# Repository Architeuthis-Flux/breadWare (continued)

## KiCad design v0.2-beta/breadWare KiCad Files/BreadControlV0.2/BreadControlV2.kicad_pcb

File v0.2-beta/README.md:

# breadWare v0.2

Here's the second board revision. I was showing the last version off to someone and they offhandedly mentioned that it would be cool if the whole thing fit under the breadboard. I knew this was my plan all along, but it forced me to finally design it before the code gets too specific to the original off-the-cuff design and I get stuck with my poor ~~life~~ design choices. 

## Matrix Board Changes

I found that the most valuable resource when finding paths between rows that aren't directly connected (so they need to make an intermediate hop) are "virtual" breadboard rows that aren't connected to the actual board but connect to the control board below and basically act as the general purpose nodes to do everything else (like reading voltages, connecting to the GPIO on the microcontroller, connecting to a second board, etc.). I put 4 of them in (on chips A, D, E, H), and I don't think that's nearly enough if I want to be able to do a bunch of special function things at once without making the user use some particular set of rows to do certain things. I would really like to make it as simple as "put anything wherever and the board will figure it out."

I changed the logical arrangement of the [MT8816](https://www.futurlec.com/Datasheet/Zarlink/MT8816AE.pdf) crosspoint switches to make the it easier to just hop over the middle space. In the original layout if I wanted to connect top row 5 to bottom row 5, it would always take 2 hops to do that (and these switches each have an on resistance of about 65Ω). Now the bottom rows are flipped so internally the bottom left is 62 and counts down to 33 on the right (note: these are abstracted away to the user by using b1-b30 instead of bigger numbers.)

And just to add some glam I added some reverse mounted LEDs that shine through the top and bottom power rails to show when that rail's power supply is on.

## Control Board Changes

I almost entirely redesigned the controller board so it has a ton of whatever the hardware equivalent of syntactic sugar is. The original was kind of thrown together to make sure the concept of using crosspoint switches like that wasn't fundamentally stupid (still not entirely ruling that out, but so far it looks promising.) I also just realized I never did a writeup for the first iteration, and I'm not about to go back and do that just to prove that this board is an improvement.

### Power Stuff
Because I'm going to such great lengths to make everything analog, and I already need a negative supply for the crosspoint switches; I decided to make the adjustable power supply for the rails also be able to do negative voltages. The power stuff still needs some work, right now it gets pretty warm when it's running and it really doesn't like it when I remove the matrix board with it on. Presumably because it needs some current draw but I'm not exactly sure why it cares as much as it does (I burned a tantalum cap shaped brand into my finger, you could almost read the markings in it.) 

Also, the range of voltages available to each of the 4 rails is fixed. Next revision might include some way to multiplex the power rails (allowing any of them to be negative, right now only the bottom negative rail can do that and it can be changed with a solder jumper) but having looked into it for a while, there doesn't seem to be a way to do it simply enough to outweigh the small utility gained from it. If anyone knows a better way to do this, let me know.

I'm using an [LT1054](https://www.ti.com/lit/ds/symlink/lt1054.pdf?ts=1623386605661&ref_url=https%253A%252F%252Fwww.ti.com%252Fproduct%252FLT1054%253Futm_source%253Dgoogle%2526utm_medium%253Dcpc%2526utm_campaign%253Dapp-null-null-GPN_EN-cpc-pf-google-sa%2526utm_content%253DLT1054%2526ds_k%253DLT1054%2526DCM%253Dyes%2526gclid%253DCj0KCQjw8IaGBhCHARIsAGIRRYqazWa1HYDDSNdHtIH7dqU-yqDqCnm6CfqRnDNBBC_sS4i2s7MQtgcaAuJ-EALw_wcB%2526gclsrc%253Daw.ds) switched capacitor bipolar voltage converter that takes in +5V and doubles it to +10V and also flips that to -10V. That powers the MT8816s directly and the op amps I'm using for the adjustable voltage supplies. The previous board used inductors for that, and aside from the electrical noise, you could hear them running. I know the frequency they run at is way higher than 20kHz but they must have been resonating with something (or I'm actually part bat) because it was super annoying.

The way I decided to make an adjustable supply that can be controlled by the mcu might be really dumb, but so far it seems to work. I didn't find any well documented examples of people doing it this way, so I'd love to hear from anyone who has or has a good reason why it will cause problems. 

I used an [MCP4728](http://ww1.microchip.com/downloads/en/devicedoc/22187e.pdf) DAC that's controlled by I2C and feeds it's 4 outputs into 2 [L272D](https://www.st.com/resource/en/datasheet/l272.pdf) power op amps that can apparently supply 1A each. I used the inverting arrangement with a gain of 1.6 to make the negative supply able to supply 0V - -8V from the 0V - +5V output from the DAC. I put a bunch of low voltage drop schottkys (or is it schottkies? weird) so whatever is happening on the power rails they're supplying shouldn't affect them too much. 

What's cool about this setup is that the DAC is fast enough to use this whole circuit as a DDS function generator. That's why I put solder jumpers to disconnect all the bypass caps. I haven't written the code to try this out yet though. 

### Special Functions

On the control board there's another 8x16 crosspoint switch that I'm using to multiplex the 8 passthrough connections (1 per chip on the top matrix board, but only 4 of them aren't connected to a breadboard pin) to the special functions on the bottom control board. 

The special functions are (a checkmark means the firmware is written enough to use it):
 [  ] 2 ADC channels that can be read by the microcontroller 
 [x] 2 digital potentiometer channels using an [MCP4661](https://ww1.microchip.com/downloads/en/DeviceDoc/22107B.pdf) 
 [  ] 5 GPIO pins directly connected to the [ATmega4809](http://ww1.microchip.com/downloads/en/DeviceDoc/ATmega4808-4809-Data-Sheet-DS40002173A.pdf)
 [x] 2 adjustable power supply channels (0 - 5V, 0 - -8V)
 [x] 1 ground

The 2 ADC channels go through two 4:1 voltage dividers to bring a possible ±10V input down to ±2.5V and the bottom of those dividers are connected to the V_REF pin on the microcontroller so analog signals can be biased to 0-5V to be read by the 10-bit ADC. 

There's an [MCP4661](https://ww1.microchip.com/downloads/en/DeviceDoc/22107B.pdf) dual 8 bit digital potentiometer that has all 3 pins on 2 independent pots connected to the special function switch. I need to come up with a better interface for setting it in the terminal menu. When I eventually get around to making a GUI for this it will definitely make these more useful. These also come in 4 different ranges (5K, 10K, 50K, 100K) with the same pinout, I currently have the 50K model in there so that means each step is 195 ohms.

The GPIO pins are super interesting, for some reason the [ATmega4809](http://ww1.microchip.com/downloads/en/DeviceDoc/ATmega4808-4809-Data-Sheet-DS40002173A.pdf) datasheet never mentions the clear superiority of the first 4 pins in port C. 

PC0-3 can do I2C, U(S)ART, 16-bit Timer/Counter, PWM, SPI, and CCL-LUT! 
The CCL-LUT means Configurable Custom Logic - LookUp Table, so that means it an simulate an arbitrary logic gate. The analog stuff is covered by pin PE3. 

Now the tricky part is coming up with a nice way to use those functions through the serial connection. I could probably somehow port the Bus Pirate firmware into some sort of shell, so you could use their awesome Community Firmware (and the red PCB really sells the aesthetic.) 

Also, if anyone from Dangerous Prototypes is reading this; I'm dying for updates on (or just an official crushing of my dreams of one day owning) the [Bus Pirate Ultra](http://dangerousprototypes.com/forum/index.php?topic=10316.0)

### Communicating With Other Things

On each corner of the board I put a 2x2 header so you can connect these side-by-side and make these into longer board. They communicate via UART with Tx Rx in at the top left and Tx Rx out at the top right. The bottom corners have the 4 unconnected pins from the top matrix on both sides. So you could use these to make connections from one board to the other. As it is currently, having only 4 of these general purpose matrix connections is a huge bottleneck for doing just about anything so I probably need to come up with a way to have more of these free pins in the next revision. 

To communicate with the computer, I'm using an [MCP2221A](http://ww1.microchip.com/downloads/en/devicedoc/20005565b.pdf) to talk to the mcu via a dedicated UART. That chip is also connected to the I2C lines but I'm not sure what I'm going to use that for, maybe I'll have the I2C traffic passed along in some sort of debug mode. It also can send a reset signal from one of it's 4 GPIO lines to the ATmega4809 (with a solder jumper in case that causes problems), which notably is a missing feature of this chip. 
I could pretend that my choice to to use this was some principled stand against FTDI to cover for the fact that I actually don't remember why I chose this over and FTDI232.

## Making It Do Stuff

The interface currently sort of follows the general format that a Bus Pirate (and I'm sure a bunch of other things) use; mostly single character commands that present a sub menu. It's amazing how quickly you run out of letters that make sense for a particular command, especially when you have some command you want to be available globally. 

Making connections on the board just requires you to type in the two rows you want to connect, separated by a comma. Rows on the bottom are preceded by a 'b' so if you want to connect the 12th row on the top to the 24th row on the bottom you just type
 > 12,b24

In the near future I intend to make a full blown GUI for this, because that's the part that will make this thing actually make your life easier.

Here are some screenshots the interface:

Connecting Nodes

Disconnecting Nodes

Turning on the power supplies

Using the potentiometer

Showing the frontend connections you've made

Showing the backend (chip to chip) connections

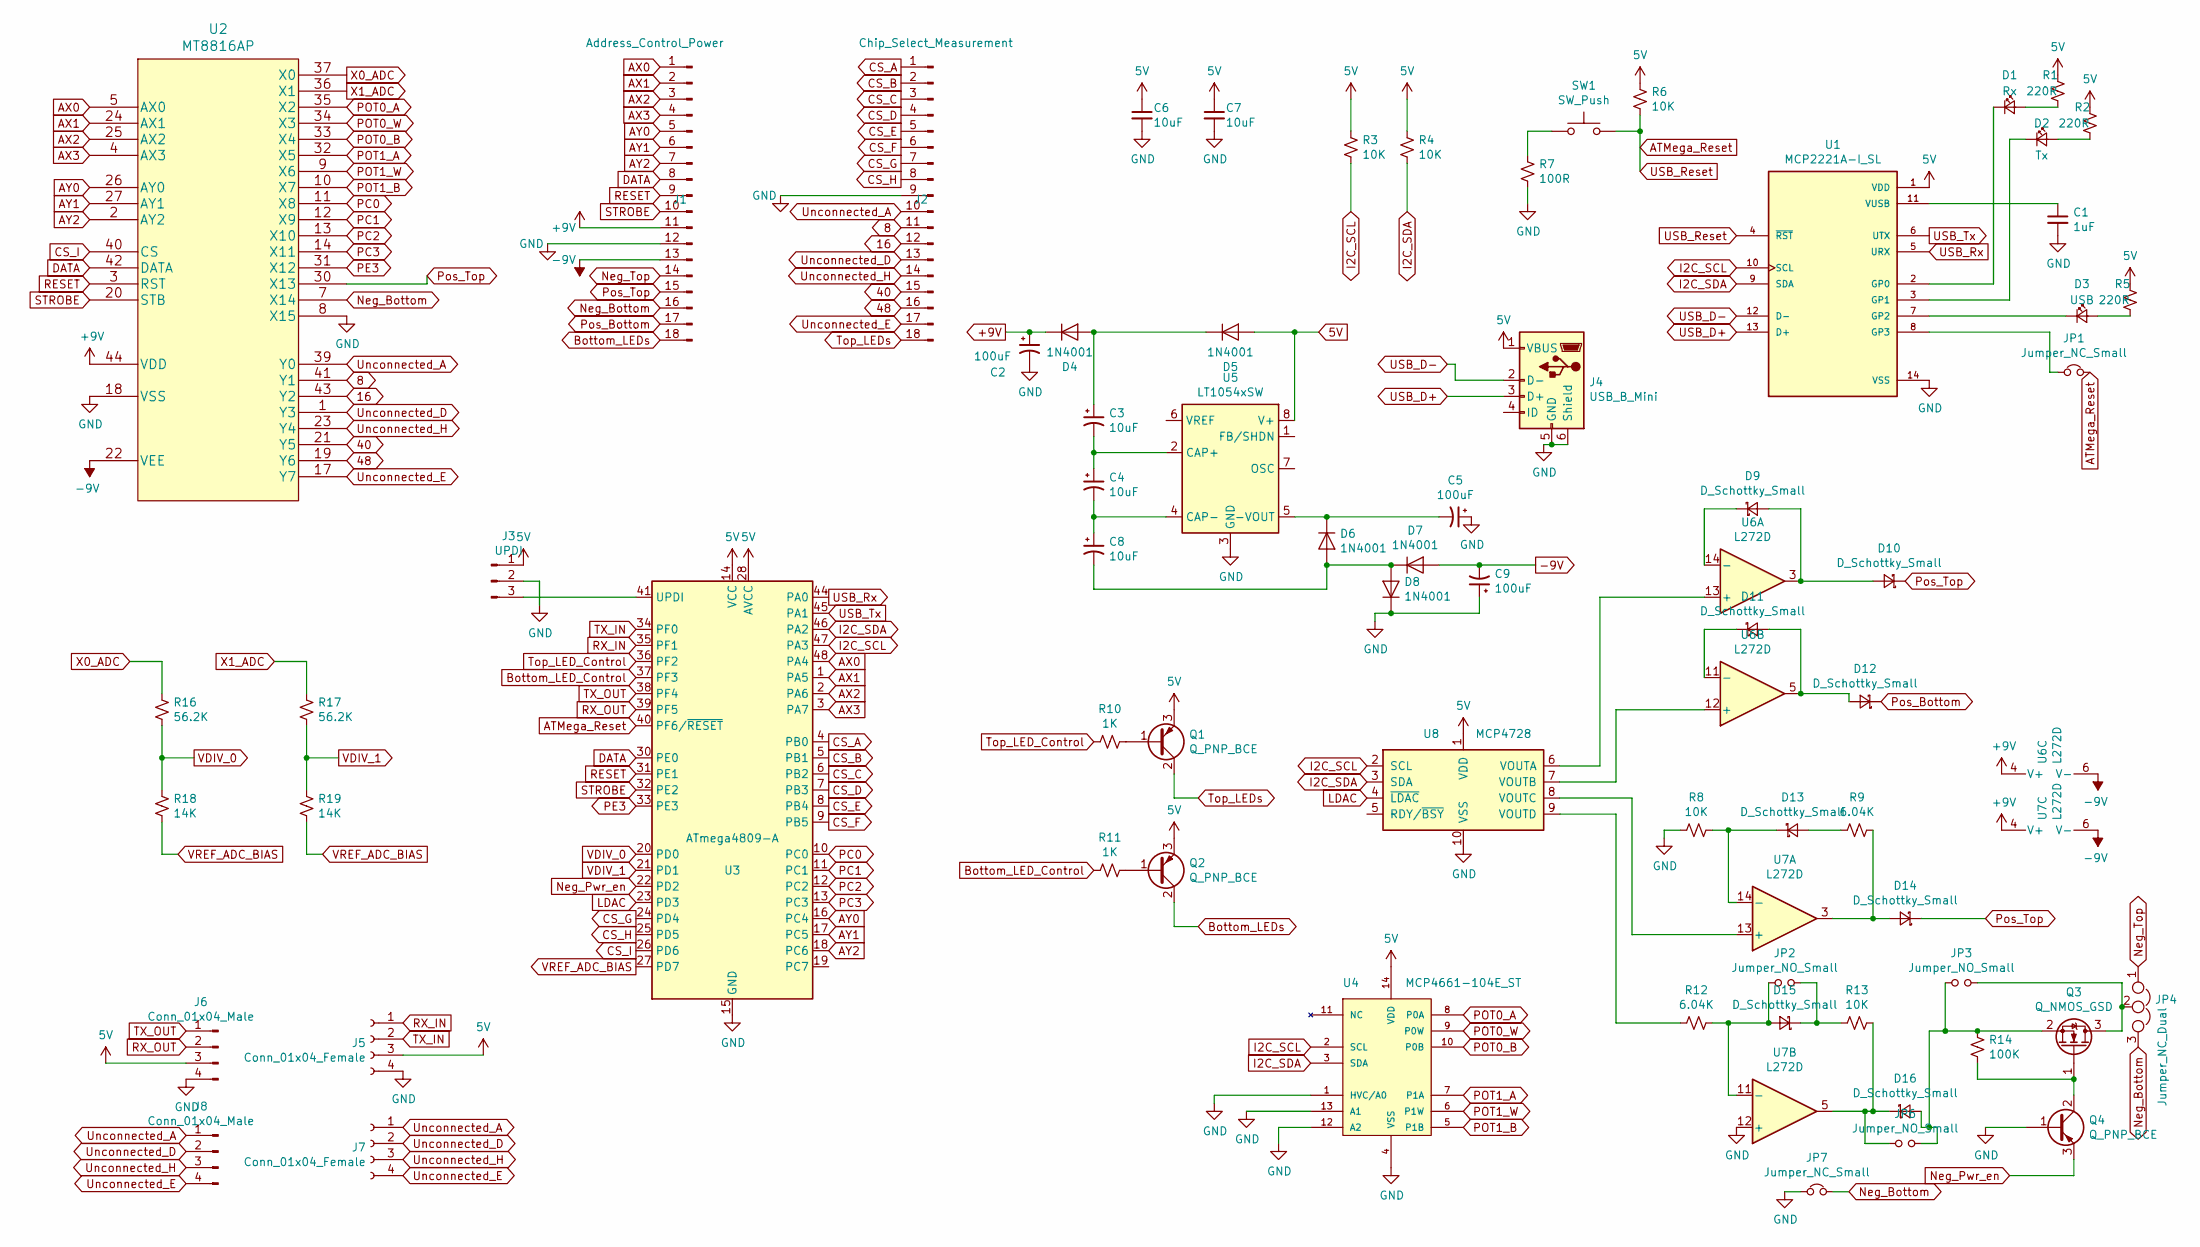
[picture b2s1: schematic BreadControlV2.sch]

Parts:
C1: 1uF; C_0805_2012Metric_Pad1.15x1.40mm_HandSolder
C2, C5, C9: 100uF; C_1206_3216Metric_Pad1.42x1.75mm_HandSolder
C3, C4, C8: 10uF; CP_EIA-6032-20_AVX-F_Pad2.25x2.35mm_HandSolder
C6, C7: 10uF; C_0805_2012Metric_Pad1.15x1.40mm_HandSolder
D1: Rx; D_0603_1608Metric_Pad1.05x0.95mm_HandSolder
D2: Tx; D_0603_1608Metric_Pad1.05x0.95mm_HandSolder
D3: USB; D_0603_1608Metric_Pad1.05x0.95mm_HandSolder
D4, D5, D6, D7, D8: 1N4001; D_SOD-123
D9, D10, D11, D12, D13, D14, D15, D16: D_Schottky_Small; D_SMB
J1: Address_Control_Power; PinHeader_1x18_P2.54mm_Vertical
J2: Chip_Select_Measurement; PinHeader_1x18_P2.54mm_Vertical
J3: UPDI; PinHeader_1x03_P2.54mm_Vertical
J4: USB_B_Mini; AMPHENOL_10033526-N3212LF
J5, J7: Conn_01x04_Female; PinHeader_2x02_P2.54mm_Horizontal
J6, J8: Conn_01x04_Male; PinHeader_2x02_P2.54mm_Horizontal
JP1, JP7: Jumper_NC_Small; SolderJumper-2_P1.3mm_Bridged_RoundedPad1.0x1.5mm
JP2, JP3, JP6: Jumper_NO_Small; SolderJumper-2_P1.3mm_Open_RoundedPad1.0x1.5mm
JP4: Jumper_NC_Dual; SolderJumper-3_P1.3mm_Bridged12_RoundedPad1.0x1.5mm_NumberL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
Q1, Q2, Q4: Q_PNP_BCE; SOT-23
Q3: Q_NMOS_GSD; SOT-23
R1, R2, R5: 220R; R_0805_2012Metric_Pad1.15x1.40mm_HandSolder
R3, R4, R6, R8, R13: 10K; R_0805_2012Metric_Pad1.15x1.40mm_HandSolder
R7: 100R; R_0805_2012Metric_Pad1.15x1.40mm_HandSolder
R9, R12: 6.04K; R_0805_2012Metric_Pad1.15x1.40mm_HandSolder
R10, R11: 1K; R_0805_2012Metric_Pad1.15x1.40mm_HandSolder
R14: 100K; R_0805_2012Metric_Pad1.15x1.40mm_HandSolder
R16, R17: 56.2K; R_0805_2012Metric_Pad1.15x1.40mm_HandSolder
R18, R19: 14K; R_0805_2012Metric_Pad1.15x1.40mm_HandSolder
SW1: SW_Push; SW_SPST_PTS645
U1: MCP2221A-I_SL; SOIC-14_3.9x8.7mm_P1.27mm
U2: MT8816AP; PLCC-44_16.6x16.6mm_P1.27mm
U3: ATmega4809-A; TQFP-48_7x7mm_P0.5mm
U4: MCP4661-104E_ST; TSSOP-14_4.4x5mm_P0.65mm; MPN MCP4661-104E/ST
U5: LT1054xSW; SOIC-16W_7.5x10.3mm_P1.27mm
U6, U7: L272D; SOIC-16_3.9x9.9mm_P1.27mm
U8: MCP4728; MSOP-10_3x3mm_P0.5mm

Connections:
5V: C6.1, C7.1, D5.2 (A), J3.1, J4.1 (VBUS), J5.3, J6.3, Q1.3 (E), Q2.3 (E), R1.1, R2.1, R3.1, R4.1, R5.1, R6.1, U1.1 (VDD), U3.14 (VCC), U3.28 (AVCC), U3.42 (VCC), U4.14 (VDD), U5.8 (V+), U8.1 (VDD)
8: J2.11, U2.41 (Y1)
16: J2.12, U2.43 (Y2)
40: J2.15, U2.21 (Y5)
48: J2.16, U2.19 (Y6)
+9V: C2.1, D4.1 (K), J1.11, U2.44 (VDD), U6.4 (V+), U7.4 (V+)
-9V: C9.2, D7.2 (A), J1.13, U2.22 (VEE), U6.6 (V-), U7.6 (V-)
ATMega_Reset: JP1.2, R6.2, SW1.2, U1.4 (~RST), U3.40 (PF6/~RESET)
AX0: J1.1, U2.5 (AX0), U3.48 (PA4)
AX1: J1.2, U2.24 (AX1), U3.1 (PA5)
AX2: J1.3, U2.25 (AX2), U3.2 (PA6)
AX3: J1.4, U2.4 (AX3), U3.3 (PA7)
AY0: J1.5, U2.26 (AY0), U3.16 (PC4)
AY1: J1.6, U2.27 (AY1), U3.17 (PC5)
AY2: J1.7, U2.2 (AY2), U3.18 (PC6)
Bottom_LED_Control: R11.2, U3.37 (PF3)
Bottom_LEDs: J1.18, Q2.2 (C)
CS_A: J2.1, U3.4 (PB0)
CS_B: J2.2, U3.5 (PB1)
CS_C: J2.3, U3.6 (PB2)
CS_D: J2.4, U3.7 (PB3)
CS_E: J2.5, U3.8 (PB4)
CS_F: J2.6, U3.9 (PB5)
CS_G: J2.7, U3.24 (PD4)
CS_H: J2.8, U3.25 (PD5)
CS_I: U2.40 (CS), U3.26 (PD6)
DATA: J1.8, U2.42 (DATA), U3.30 (PE0)
GND: C1.2, C2.2, C5.1, C6.2, C7.2, C9.1, D8.1 (K), J1.12, J2.9, J3.2, J4.5 (GND), J4.6 (Shield), J5.4, J6.4, JP7.1, Q4.1 (B), R7.2, R8.1, U1.14 (VSS), U2.8 (X15), U2.18 (VSS), U3.15 (GND), U3.29 (GND), U3.43 (GND), U4.1 (HVC/A0), U4.4 (VSS), U4.12 (A2), U4.13 (A1), U5.3 (GND), U7.12 (+), U8.10 (VSS)
I2C_SCL: R3.2, U1.10 (SCL), U3.47 (PA3), U4.2 (SCL), U8.2 (SCL)
I2C_SDA: R4.2, U1.9 (SDA), U3.46 (PA2), U4.3 (SDA), U8.3 (SDA)
LDAC: U3.23 (PD3), U8.4 (~LDAC)
Neg_Bottom: J1.16, JP4.3, JP7.2, U2.7 (X14)
Neg_Pwr_en: Q4.3 (E), U3.22 (PD2)
Neg_Top: J1.14, JP4.1
unnamed: C1.1, U1.11 (VUSB)
unnamed: C3.1, D4.2 (A), D5.1 (K)
unnamed: C3.2, C4.1, U5.2 (CAP+)
unnamed: C4.2, C8.1, U5.4 (CAP-)
unnamed: C5.2, D6.1 (K), U5.5 (-VOUT)
unnamed: C8.2, D6.2 (A), D7.1 (K), D8.2 (A)
unnamed: D1.1 (K), U1.2 (GP0)
unnamed: D1.2 (A), R1.2
unnamed: D2.1 (K), U1.3 (GP1)
unnamed: D2.2 (A), R2.2
unnamed: D3.1 (K), U1.7 (GP2)
unnamed: D3.2 (A), R5.2
unnamed: D9.1 (K), U6.14 (-)
unnamed: D9.2 (A), D10.2 (A), U6.3
unnamed: D11.1 (K), U6.11 (-)
unnamed: D11.2 (A), D12.2 (A), U6.5
unnamed: D13.1 (K), R8.2, U7.14 (-)
unnamed: D13.2 (A), R9.1
unnamed: D14.2 (A), R9.2, U7.3
unnamed: D15.1 (K), JP2.2, R13.1
unnamed: D15.2 (A), JP2.1, R12.2, U7.11 (-)
unnamed: D16.1 (K), JP6.1, R13.2, U7.5
unnamed: D16.2 (A), JP3.1, JP6.2, Q3.2 (S), R14.1
unnamed: J3.3, U3.41 (UPDI)
unnamed: JP1.1, U1.8 (GP3)
unnamed: JP3.2, JP4.2, Q3.3 (D)
unnamed: Q1.1 (B), R10.1
unnamed: Q2.1 (B), R11.1
unnamed: Q3.1 (G), Q4.2 (C), R14.2
unnamed: R7.1, SW1.1
unnamed: R12.1, U8.9 (VOUTD)
unnamed: U6.12 (+), U8.7 (VOUTB)
unnamed: U6.13 (+), U8.6 (VOUTA)
unnamed: U7.13 (+), U8.8 (VOUTC)
PC0: U2.11 (X8), U3.10 (PC0)
PC1: U2.12 (X9), U3.11 (PC1)
PC2: U2.13 (X10), U3.12 (PC2)
PC3: U2.14 (X11), U3.13 (PC3)
PE3: U2.31 (X12), U3.33 (PE3)
POT0_A: U2.35 (X2), U4.8 (P0A)
POT0_B: U2.33 (X4), U4.10 (P0B)
POT0_W: U2.34 (X3), U4.9 (P0W)
POT1_A: U2.32 (X5), U4.7 (P1A)
POT1_B: U2.10 (X7), U4.5 (P1B)
POT1_W: U2.9 (X6), U4.6 (P1W)
Pos_Bottom: D12.1 (K), J1.17
Pos_Top: D10.1 (K), D14.1 (K), J1.15, U2.30 (X13)
RESET: J1.9, U2.3 (RST), U3.31 (PE1)
RX_IN: J5.1, U3.35 (PF1)
RX_OUT: J6.2, U3.39 (PF5)
STROBE: J1.10, U2.20 (STB), U3.32 (PE2)
TX_IN: J5.2, U3.34 (PF0)
TX_OUT: J6.1, U3.38 (PF4)
Top_LED_Control: R10.2, U3.36 (PF2)
Top_LEDs: J2.18, Q1.2 (C)
USB_D+: J4.3 (D+), U1.13 (D+)
USB_D-: J4.2 (D-), U1.12 (D-)
USB_Rx: U1.5 (URX), U3.44 (PA0)
USB_Tx: U1.6 (UTX), U3.45 (PA1)
Unconnected_A: J2.10, J7.1, J8.1, U2.39 (Y0)
Unconnected_D: J2.13, J7.2, J8.2, U2.1 (Y3)
Unconnected_E: J2.17, J7.4, J8.4, U2.17 (Y7)
Unconnected_H: J2.14, J7.3, J8.3, U2.23 (Y4)
VDIV_0: R16.2, R18.1, U3.20 (PD0)
VDIV_1: R17.2, R19.1, U3.21 (PD1)
VREF_ADC_BIAS: R18.2, R19.2, U3.27 (PD7)
X0_ADC: R16.1, U2.37 (X0)
X1_ADC: R17.1, U2.36 (X1)

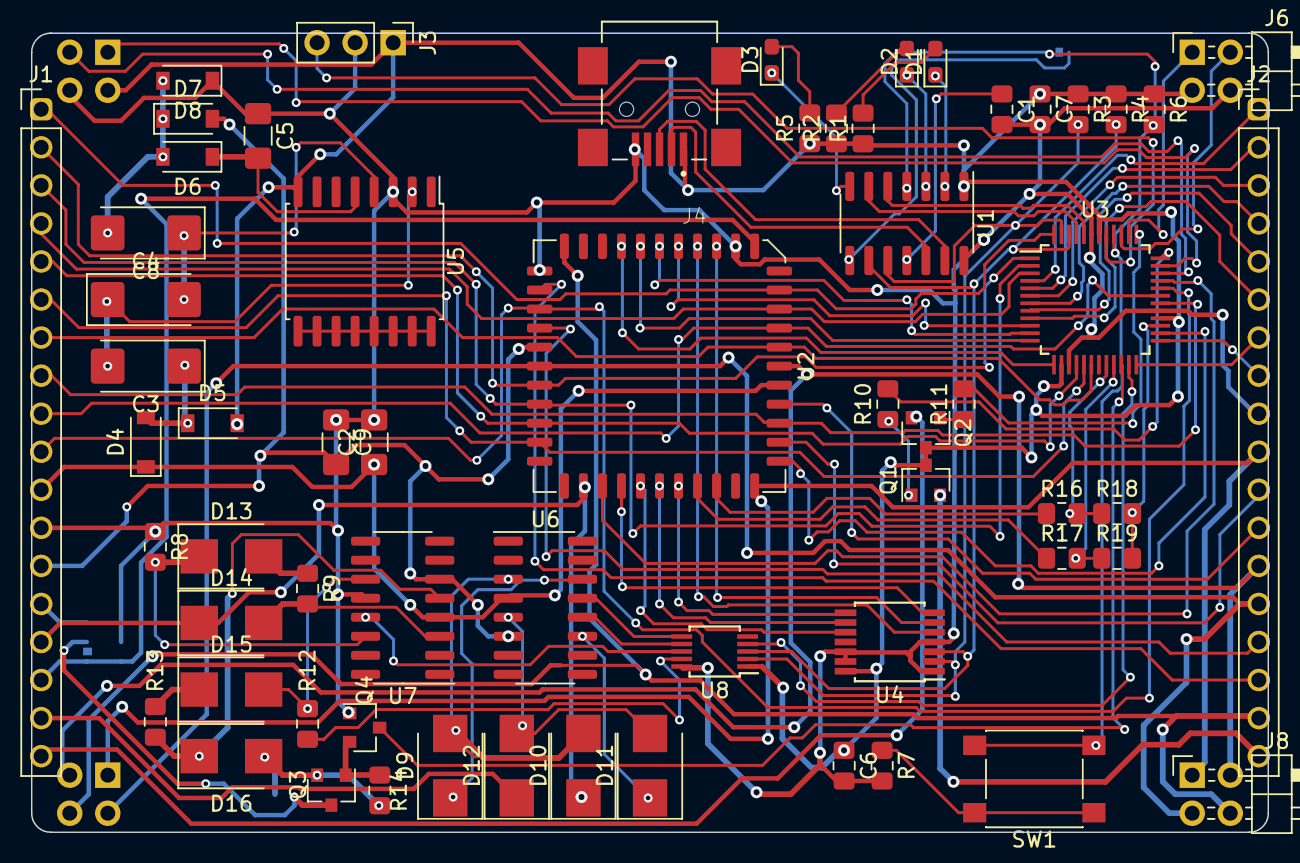
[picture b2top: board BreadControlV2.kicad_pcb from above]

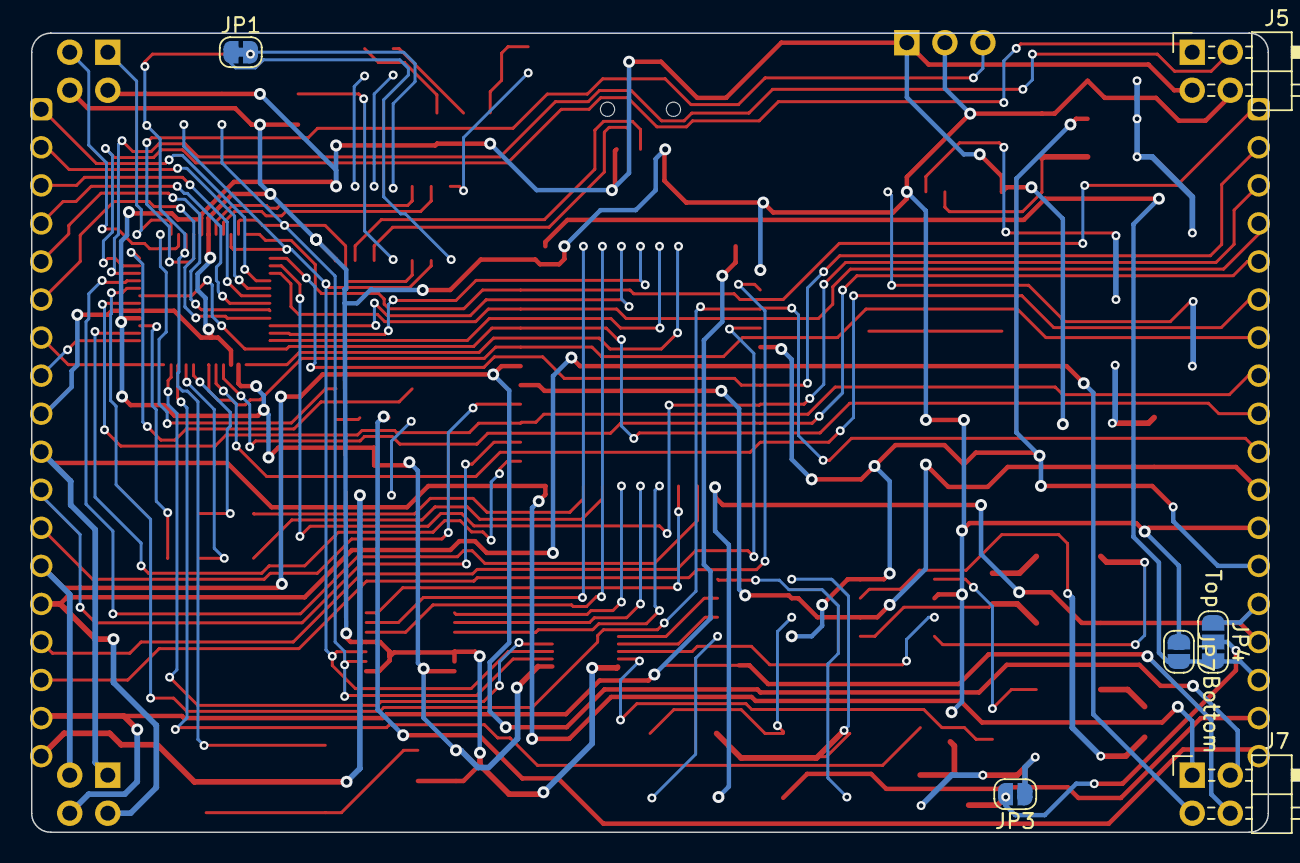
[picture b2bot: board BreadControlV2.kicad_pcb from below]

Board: 2 copper layers, 82.6 x 53.3 mm, 68 parts (6 on the bottom side), 102 nets.
